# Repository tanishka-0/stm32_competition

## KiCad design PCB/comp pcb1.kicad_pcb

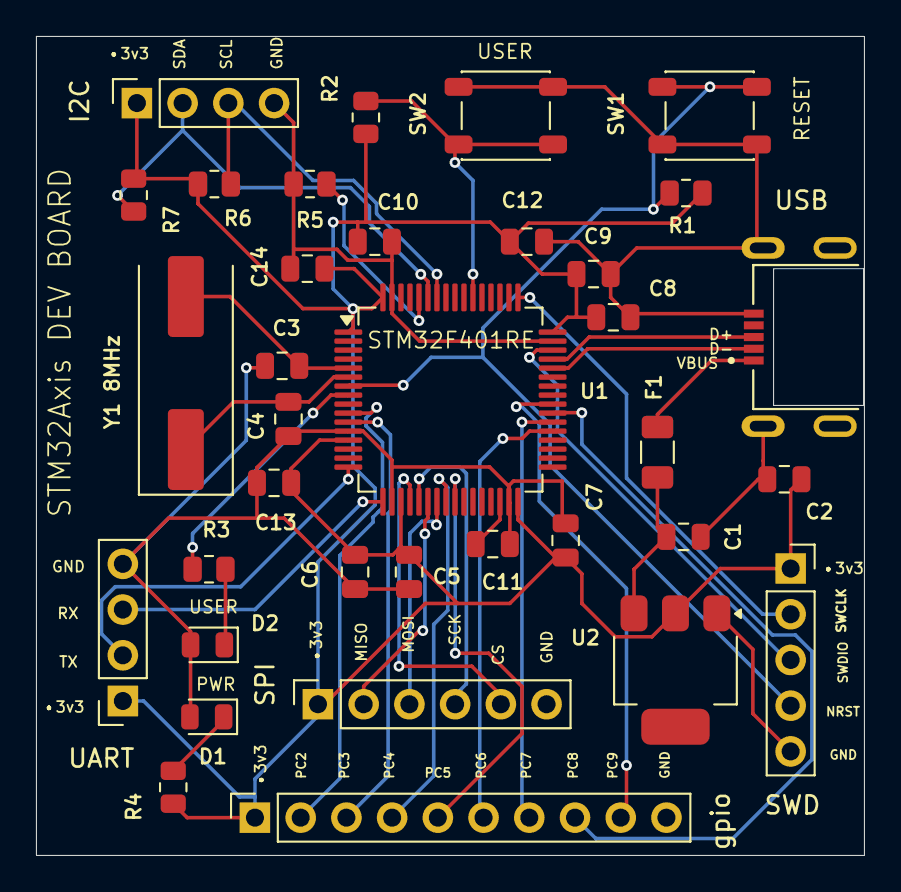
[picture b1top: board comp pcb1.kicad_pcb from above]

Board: 2 copper layers, 46.0 x 45.5 mm, 35 parts (0 on the bottom side), 33 nets.

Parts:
C1, C2: 10µF; C_0805_2012Metric
C3, C4: C; C_0805_2012Metric
C5, C6, C7, C8, C9, C10, C14: 100nF; C_0805_2012Metric
C11, C12: 4.7µF; C_0805_2012Metric
C13: 1µF; C_0805_2012Metric
D1: pwLED; LED_0805_2012Metric
D2: userLED; LED_0805_2012Metric
F1: fuse; Fuse_1206_3216Metric
I2C: I2C; PinSocket_1x04_P2.54mm_Vertical
R1, R2, R5: 10kΩ; R_0805_2012Metric
R3: 330Ω; R_0805_2012Metric
R4: 1kΩ; R_0805_2012Metric
R6, R7: 4.7kΩ; R_0805_2012Metric
SPI: SPI; PinSocket_1x06_P2.54mm_Vertical
SW1, SW2: SW_Push; SW_SPST_PTS647_Sx38
SWD: SWD; PinSocket_1x05_P2.54mm_Vertical
U1: STM32F401RETx; LQFP-64_10x10mm_P0.5mm
U2: regulartor; SOT-223
UART: UART; PinSocket_1x04_P2.54mm_Vertical
USB: USB; MOLEX_47642-0001
Y1 8MHz: 8MHz; Crystal_SMD_HC49-SD
gpio: gpio_exp; PinSocket_1x10_P2.54mm_Vertical

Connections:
/CS: SPI.5, U1.20 (PA4)
/D+: U1.45 (PA12), USB.3 (D+)
/D-: U1.44 (PA11), USB.2 (D-)
/G1: U1.10 (PC2), gpio.2
/G2: U1.11 (PC3), gpio.3
/G3: U1.24 (PC4), gpio.4
/G4: U1.25 (PC5), gpio.5
/G5: U1.37 (PC6), gpio.6
/G6: U1.38 (PC7), gpio.7
/G7: U1.39 (PC8), gpio.8
/G8: U1.40 (PC9), gpio.9
/MISO: SPI.2, U1.22 (PA6)
/MOSI: SPI.3, U1.23 (PA7)
/O1: R1.2, SW1.1, SWD.4, U1.7 (NRST)
/O2: R2.2, SW2.1, U1.54 (PD2)
/O3: R3.1, U1.8 (PC0)
/RX: U1.17 (PA3), UART.3
/SCK: SPI.4, U1.21 (PA5)
/SCL: I2C.3, R6.1, U1.58 (PB6)
/SDA: I2C.2, R7.1, U1.59 (PB7)
/SWCLK: SWD.2, U1.49 (PA14)
/SWDIO: SWD.3, U1.46 (PA13)
/TX: U1.16 (PA2), UART.2
/Vreg: C2.1, C5.1, C6.1, C7.1, C8.1, C9.1, C10.1, C12.1, C13.1, C14.1, I2C.1, R1.1, R2.1, R4.1, R6.2, R7.2, SPI.1, SWD.1, U1.1 (VBAT), U1.13 (VREF+), U1.19 (VDD), U1.32 (VDD), U1.48 (VDD), U1.64 (VDD), U2.2 (VO), UART.1, gpio.1
GND: C1.2, C2.2, C3.1, C4.2, C5.2, C6.2, C7.2, C8.2, C9.2, C10.2, C11.1, C12.2, C13.2, C14.2, D1.2 (A), D2.2 (A), I2C.4, R5.1, SPI.6, SW1.2, SW2.2, SWD.5, U1.12 (VSSA), U1.18 (VSS), U1.31 (VSS), U1.47 (VSS), U1.63 (VSS), U2.1 (GND), UART.4, USB.5 (GND), USB.S1, USB.S2, USB.S3, USB.S4, gpio.10
unnamed: D1.1 (K), R4.2
unnamed: D2.1 (K), R3.2
unnamed: F1.1, USB.1 (VBUS)
unnamed: R5.2, U1.60 (BOOT0)
unnamed: C3.2, U1.5 (PH0), Y1 8MHz.2
unnamed: C4.1, U1.6 (PH1), Y1 8MHz.1
unnamed: C11.2, U1.30 (VCAP1)
unnamed: C1.1, F1.2, U2.3 (VI)
